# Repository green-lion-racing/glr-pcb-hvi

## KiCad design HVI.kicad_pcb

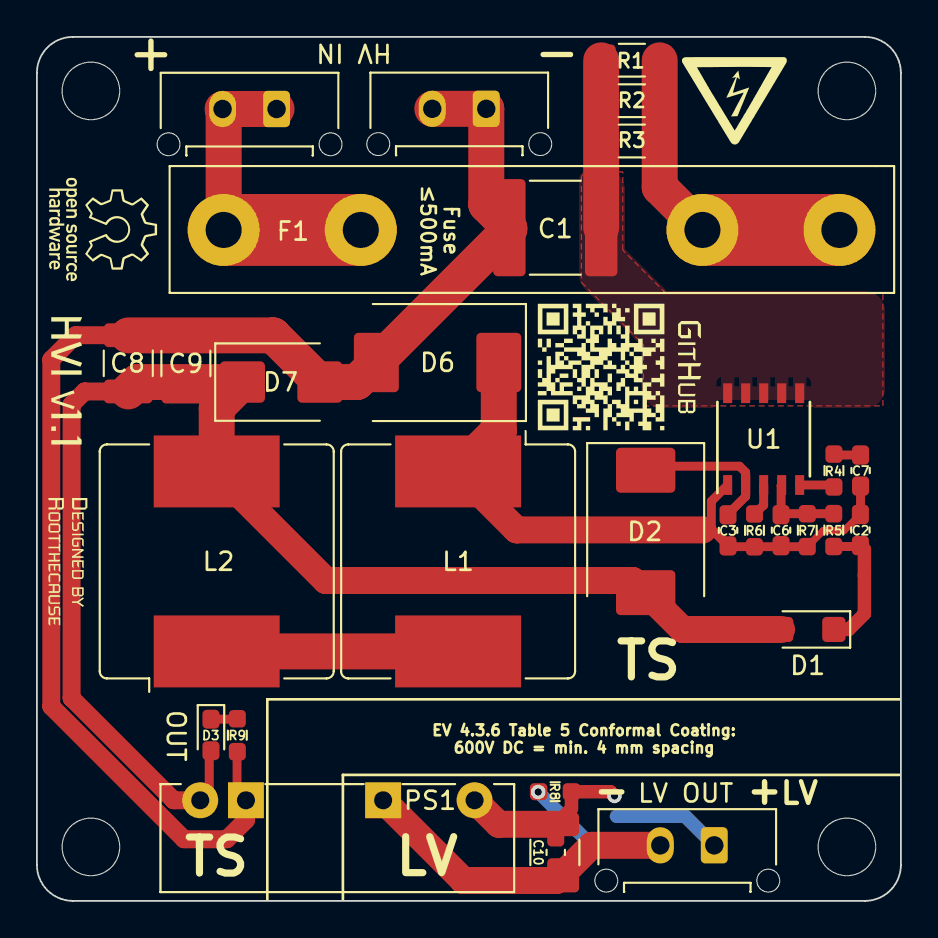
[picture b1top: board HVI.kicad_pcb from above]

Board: 2 copper layers, 48.0 x 48.0 mm, 36 parts (1 on the bottom side), 18 nets.

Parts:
C1: 220n; C_2220_5650Metric
C2, C6: 100nF; C_0603_1608Metric_Pad1.08x0.95mm_HandSolder
C3: 2.2µF; C_0603_1608Metric_Pad1.08x0.95mm_HandSolder
C7: 22nF; C_0603_1608Metric_Pad1.08x0.95mm_HandSolder
C8, C9, C11: 47µF; C_1210_3225Metric_Pad1.33x2.70mm_HandSolder
C10: 10µF; C_0603_1608Metric_Pad1.08x0.95mm_HandSolder
D1: VS-E7FX0212-M3/I; D_SMF
D2, D6: US3M-13; D_SMC
D3: LED; LED_0603_1608Metric_Pad1.05x0.95mm_HandSolder
D7: P6SMB13A; D_SMB
F1: ≤ 500 mA, solder Fuse Clips F1.1 and F1.2 and ins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; Fuseholder0,25Zoll_32mm_littlefuse_102_122
J1, J2, J3: Conn_01x02; Molex_Micro-Fit_3.0_43650-0215_1x02_P3.00mm_Vertical
JP1: SolderJumper_3_Open; SolderJumper-3_P1.3mm_Open_RoundedPad1.0x1.5mm_NumberLabels
L1, L2: 4.7 mH; L_Bourns_SRR1208_12.7x12.7mm
MK1, MK2, MK3, MK4: Mounting_Hole; MountingHole_3.2mm_M3_DIN965
PS1: RP-1205S; CONV_PEME1-S5-S5-S
R1, R2, R3: 270; R_1206_3216Metric_Pad1.30x1.75mm_HandSolder
R4: 1k; R_0603_1608Metric_Pad0.98x0.95mm_HandSolder
R5: 27k; R_0603_1608Metric_Pad0.98x0.95mm_HandSolder
R6: -; R_0603_1608Metric_Pad0.98x0.95mm_HandSolder
R7: 10k; R_0603_1608Metric_Pad0.98x0.95mm_HandSolder
R8: 150; R_0603_1608Metric_Pad0.98x0.95mm_HandSolder
R9: 4k7; R_0603_1608Metric_Pad0.98x0.95mm_HandSolder
U1: VIPER06-SSOP-10; SSOP-10_3.9x4.9mm_P1.00mm

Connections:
unnamed: C1.1, R1.1, R2.1, R3.1, U1.6 (DRAIN), U1.7 (DRAIN), U1.8 (DRAIN), U1.9 (DRAIN), U1.10 (DRAIN)
unnamed: C7.1, R4.2
unnamed: C8.1, C9.1, D1.2 (A), D2.2 (A), D3.2 (A), D7.1 (A1), L2.2, PS1.1 (VIN)
unnamed: C2.1, D1.1 (K), R5.2
unnamed: C3.1, D2.1 (K), U1.2 (VDD)
unnamed: D3.1 (K), R9.2
unnamed: C1.2, C8.2, C9.2, D6.2 (A), D7.2 (A2), J3.1, J3.2, PS1.2 (GND), R9.1
unnamed: C2.2, C3.2, C6.2, C7.2, D6.1 (K), L1.1, R6.2, R7.2, U1.1 (GND)
unnamed: F1.2, R1.2, R2.2, R3.2
unnamed: J1.1, JP1.2 (C)
unnamed: C10.2, C11.2, J1.2, PS1.5 (0V)
unnamed: F1.1, J2.1, J2.2
unnamed: C10.1, C11.1, JP1.1 (A), PS1.7 (+VOUT), R8.1
unnamed: JP1.3 (B), R8.2
unnamed: L1.2, L2.1
unnamed: R4.1, U1.5 (COMP)
unnamed: C6.1, R5.1, R7.1, U1.4 (FB)
unnamed: R6.1, U1.3 (LIM)
